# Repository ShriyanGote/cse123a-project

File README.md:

# 123a-project: Smart Pitcher Base

This repo contains all the code, hardware notes, and documentation for our Smart Pitcher Base project. The system is made up of three pieces:

1. **ESP32C3 firmware** — reads the load cell (HX711) on the pitcher base and POSTs readings to the web server.
2. **Web server / dashboard** — a Vite + React app (deployed on Vercel) that ingests readings into Supabase. Account sign-in and a setup guide live at https://cse123a-project-6a3s.vercel.app/.
3. **Mobile app** — an Expo / React Native app that talks to the web server, displays the water level, and receives low-water push notifications.

Everything lives under [`Code/`](Code). Each sub-project has its own README with run instructions.

```
Code/
├── ESP32/         # firmware (ESP-IDF)
├── web-server/    # Vite + React dashboard + Vercel API routes
├── mobile-app/    # Expo / React Native app
└── 3D Designs/    # printable parts for the base
```

---

# Other things in this repo

- [Documentation/](Documentation) — write-ups and design docs
- [Hardware Notes/](Hardware%20Notes) — schematics, PCB revisions, wiring notes
- [HardwarePicture/](HardwarePicture) — photos of the assembled hardware
- [Meeting Notes/](Meeting%20Notes) — weekly meeting notes
- [Status Updates/](Status%20Updates) — milestone / status reports
- [Code/Links to Test Cases.md](Code/Links%20to%20Test%20Cases.md) — index of test cases
- `git-contribution-report.sh` + `aliases.json` + `folders.json` — helpers for generating per-author contribution metrics

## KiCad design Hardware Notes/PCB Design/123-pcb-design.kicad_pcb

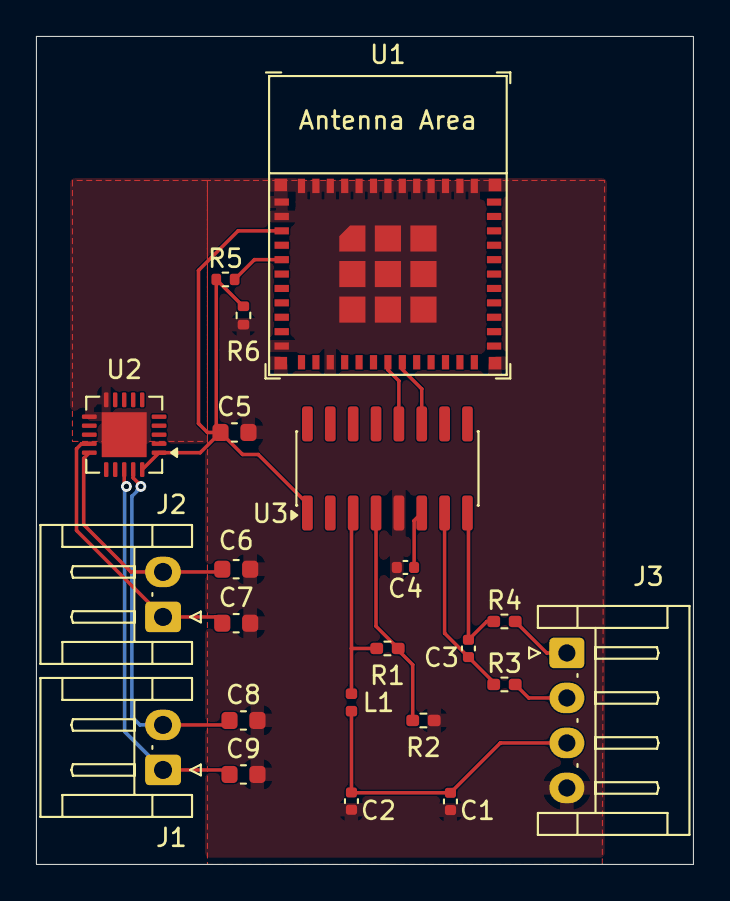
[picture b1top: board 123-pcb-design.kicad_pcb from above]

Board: 2 copper layers, 36.5 x 46.0 mm, 22 parts (0 on the bottom side), 17 nets.

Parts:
C1, C3, C4: 0.1μF; C_0402_1005Metric
C2: 10μF; C_0402_1005Metric
C5, C6, C7: 4.7μF; C_0603_1608Metric
C8, C9: 10μF; C_0603_1608Metric
J1, J2: JST 1x02; JST_EH_S2B-EH_1x02_P2.50mm_Horizontal
J3: JST 1x04; JST_EH_S4B-EH_1x04_P2.50mm_Horizontal
L1: 3.3μH; L_0402_1005Metric
R1, R2: 20k; R_0402_1005Metric_Pad0.72x0.64mm_HandSolder
R3, R4: 100; R_0402_1005Metric_Pad0.72x0.64mm_HandSolder
R5: 100k; R_0402_1005Metric
R6: 100K; R_0402_1005Metric
U1: ESP32-C3-MINI-1
U2: MCP73871; QFN-20-1EP_4x4mm_P0.5mm_EP2.5x2.5mm
U3: HX711; SOIC-16_3.9x9.9mm_P1.27mm

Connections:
GND: C1.2, C2.2, C4.2, C5.2, C6.2, C7.2, C8.2, C9.2, J3.4, R2.2, R6.2, U1.1 (GND), U1.2 (GND), U1.11 (GND), U1.14 (GND), U1.36 (GND), U1.37 (GND), U1.38 (GND), U1.39 (GND), U1.40 (GND), U1.41 (GND), U1.42 (GND), U1.43 (GND), U1.44 (GND), U1.45 (GND), U1.46 (GND), U1.47 (GND), U1.48 (GND), U1.49 (GND), U1.50 (GND), U1.51 (GND), U1.52 (GND), U1.53 (GND), U2.10 (V_{SS}), U2.11 (V_{SS}), U2.21 (V_{SS}), U3.5 (AGND)
GPIO_4/ADC_1: U1.18 (GPIO4/ADC1_CH4), U3.12 (DOUT)
GPIO_5/ADC_2: U1.19 (GPIO5/ADC2_CH0), U3.11 (PD_SCK)
J3_Pin_1: J3.1, R4.2
J3_Pin_2: J3.2, R3.2
J3_Pin_3: C1.1, C2.1, J3.3, L1.2
unnamed: R5.2, U1.5 (GPIO2/ADC1_CH2)
unnamed: C7.1, J2.1, U2.14 (V_{BAT})
unnamed: L1.1, R1.1, U3.3 (AVDD)
unnamed: C3.2, R4.1, U3.8 (INA+)
unnamed: C3.1, R3.1, U3.7 (INA-)
unnamed: C4.1, U3.6 (VBG)
unnamed: R1.2, R2.1, U3.4 (VFB)
U2-J1_NEG: C8.1, J1.2
U2-J1_POS: C9.1, J1.1, U2.18 (IN)
U2-V_{BAT}-Pad15: C6.1, J2.2, U2.15 (V_{BAT})
VSUP: C5.1, U1.3 (3V3), U2.1 (OUT), U2.20 (OUT), U3.1 (VSUP)

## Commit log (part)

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2026-02-22 Test
2026-02-22 Create status report 5
2026-02-22 Implement firebase sdk for cloud messaging push notifications
2026-02-22 Push notification test
2026-02-24 Naming convention changes
2026-02-24 initial planning for server side calculations
2026-02-24 mac bs
2026-02-24 Adding demo script
2026-02-24 Updating Demo script
2026-02-24 updated architecture diagram
2026-02-24 Adding Engineering drawings for base plate
2026-02-24 Restructured documentation sections and updated design files
2026-02-24 fixing formating
2026-02-24 started documentation of hx711
2026-02-25 added HX711tex to design
2026-02-25 rm section made subsection
2026-02-25 Fixed names, + calibrating
2026-02-25 rm build + calibrated
2026-02-26 Shows raw data, offset, weightChange, grams not calibrated not actual grams
2026-02-26 Update Brita calibration UI
2026-02-27 Added reset calibration button
2026-02-27 Created test directory and unit tests for app
2026-02-27 Updated README with test instructions
2026-02-27 Fixing document not compiling
2026-02-27 adding my contributions to status updates
2026-02-28 Updated individual contribution for status 5
2026-02-28 adding Whats next to status report
2026-02-28 fixing spacing
2026-02-28 combo layout w/ Initial Prototype layout
2026-02-28 fixing layers and web vs phone
2026-02-28 status doc updated
2026-02-28 working on
2026-02-28 Updated what we did for status 5
2026-02-28 Updated status 5 with repo link
2026-02-28 header file prep for test code
2026-03-02 simulator file
2026-03-02 Removed fcm logic and reimplement with Push API from web-push
2026-03-02 Updating thickness to drawings
2026-03-02 Created an exploded view of the sensor with plates
2026-03-02 adding sustainablity statement
2026-03-03 Edit Architecture_Diagram.svg to remove the word ESP
2026-03-03 fixed formatting/section stuff
2026-03-03 fixed table of contents
2026-03-03 Made the plate thicker and added flat bottom
2026-03-03 tester code working
2026-03-03 Moved app test to src directory
2026-03-03 Updated Web App Section in Design Doc
2026-03-03 Added more to webapp section in design doc
2026-03-03 lineweight and separation
2026-03-03 Block Diagram included in main pdf file
2026-03-03 Updated architecture of webapp on design doc
2026-03-03 Small comments on what to add to testing section in design doc
2026-03-04 added structure, added my focus
2026-03-04 adding Aesthetic prototype section
2026-03-04 Adding pdf
2026-03-04 Updating todos
2026-03-04 Reorganized wifi provisioning code (not functional yet)
2026-03-04 fixedtypos
2026-03-05 Restructure main, ready for wifi http implement
2026-03-05 working wifi + http ?
2026-03-05 Creating Status 6
2026-03-05 HTTP POST WORKS harded code network for now
2026-03-05 modified design doc
2026-03-05 used Implementation I wrote
2026-03-05 basic collab idea
2026-03-05 Added debug statements to setupPushNotifications
2026-03-05 Add vite public key
2026-03-05 Added debug to ingest push notifications
2026-03-05 Push Debug
2026-03-05 microcontroller testing info updated
2026-03-05 updated appendix section
2026-03-05 status report updates
2026-03-05 Edit Status-6.tex
2026-03-05 Adding my contirubtions for status report
2026-03-06 Updated individual section in status 6
2026-03-07 updated status doc for submission
2026-03-07 status update
2026-03-07 finished status
2026-03-07 Doing Design for Manufacture
2026-03-09 http section
2026-03-09 section 4 of demo
2026-03-09 added to div of labor section
2026-03-09 Updated design doc
2026-03-10 Sync repo with current web app implementation
2026-03-10 Center enable notification button
2026-03-10 Added web app test section
2026-03-10 added test server for esp
2026-03-10 Added notification section to demo script
2026-03-10 Replaced all instances of esp32 and brita with appropriate terms
2026-03-10 added design obj
2026-03-10 added to design pdf
2026-03-10 added brita accident
2026-03-11 Add new file
2026-03-11 made a design for the washer
2026-03-12 documents split in two
2026-03-12 added title page
2026-03-12 Adding my individual contribituions
2026-03-12 added grams to test server display
2026-03-12 Edit Links to Test Cases
2026-03-12 Used my hotspot
2026-03-13 revision changes to prototype doc
2026-03-13 Added my individual contributions to design doc
2026-03-13 Added edge cases to test file
2026-03-13 Added unit tests for notification logic
2026-03-13 Added more edge cases
2026-03-13 Updated evaluation web app testing section
2026-03-13 Updated web app testing section
2026-03-13 Updated test cases
2026-03-13 Added executive summary
2026-03-13 team reflections
2026-03-13 Added team reflection part
2026-03-13 Remove brita from title
2026-03-13 Completed webapp functional prototype section
2026-03-13 First edit
2026-03-13 team reflections and removed mentions of esp32
2026-03-13 added detailed test cases for test plan
2026-03-13 Adding my contributions to design doc
2026-03-14 Updating renderings
2026-03-14 adding the renderings to the design doc
2026-03-14 finished wire diagram
2026-03-14 reflectipons + division of labor
2026-03-14 wiring diagram update
2026-03-14 div labor shriyan
2026-03-14 design review
2026-03-14 div of labor
2026-03-14 added link to test cases to design doc
2026-03-14 compiled design doc
2026-03-16 added overview section to demo script
2026-03-17 demo script
2026-03-18 updating demo
2026-03-18 Changed notifications to send everytime weighed value is below 20%
2026-03-18 Updated notification section in demo script
2026-03-18 adding Live demo + hardware
2026-03-18 Quick calibration refresh fix
2026-03-19 demo script w/ need and goal
2026-03-19 Add website and code repo url to Code README
2026-03-19 part 4 software changes
2026-03-19 updated pdf
2026-03-19 adding time
2026-03-19 adding time for live demo
2026-03-19 last minute update
2026-03-19 need/goal
2026-04-08 setting up document to be about production design and not prototype
2026-04-08 meeting notes
2026-04-09 attempting to add https functionality
2026-04-09 added contribution metrics script
2026-04-09 Add contribution report script
2026-04-09 Edit git-contribution-report.sh
2026-04-09 modified contribution metrics script
2026-04-11 battery charging information, mfr design updates
2026-04-11 pcb prototype setup
2026-04-11 USBC connector and HX711 wiring
2026-04-13 amplifier circuit added
2026-04-13 adding compartment for base
2026-04-13 Adding lid for compartment
2026-04-14 mobile app
2026-04-14 added 4/6 meeting notes
2026-04-14 adding exploded view with housing
2026-04-14 adding assembled_v1 design
2026-04-15 mobile app api
2026-04-16 updated to v1 circuit
2026-04-16 custom board documentation in progress
2026-04-17 updates to pcb design section
2026-04-17 added HTTPS capabilities, automatic wifi reconnection
2026-04-18 prep for tests
2026-04-18 Started tests for functions
2026-04-18 updated design for housing
2026-04-18 moved opening down
2026-04-19 design section updates and reorganizing testing/design information
2026-04-21 Implemented basic login auth, dashboard and groups
2026-04-22 removed self-hosted section, changed HTTP to HTTPS capabilities in design doc
2026-04-22 Improved dashboard and groups interface
2026-04-23 more on custom PCB added, rev2 coming by end of week
2026-04-23 Added notches to make sure the plate doesnt fall out
2026-04-23 added new base plate design
2026-04-23 Lowered the shelf
2026-04-23 simple BLE provisioning
2026-04-25 amplifier system design
2026-04-25 simplified provisioning code
2026-04-26 provisioning through https jwt jwe
2026-04-27 functionalized wifi provisioning, basic reconnect ability
2026-04-28 Updating for compartment section
2026-04-28 more ds
2026-04-28 Created screen to introduce users to the app and animated ui
2026-04-28 Changed group member cards to show user display names instead of user id
2026-04-28 Rename api route files
2026-04-28 Remove direct query from client side
2026-04-28 Remove admin role, allow ownership transfer and remove group members as owner
2026-04-29 provisioning short term reconnection, need to add long term
2026-04-29 section for housing
2026-04-29 Edit README.md
2026-04-30 base plate desing
2026-04-30 Add custom BLE provisioning flow across app, backend, and ESP firmware.
    This aligns QR/BLE onboarding with hardcoded UUIDs, token-based device registration, and ESP32 custom GATT provisioning so iOS dev builds can provision and ingest reliably.
    Made-with: Cursor
2026-04-30 Reduce web-server function count for Vercel Hobby.
    This removes legacy provisioning session endpoints and the unused mobile client helpers so the deployment can stay within the 12 serverless function limit.
    Made-with: Cursor
2026-05-01 removing files
2026-05-02 Memory saved on power loss
2026-05-02 adding test code for api for web-server
2026-05-02 made top plate wider
2026-05-03 board rev3
2026-05-05 poster file added
2026-05-05 Updated design/renamed designs
2026-05-05 added hole for wire passthrough
2026-05-05 making walls higher'
2026-05-06 removing 2
2026-05-06 Adding feature where users can deactive/activite their accounts via web-app
2026-05-06 Adding guide
2026-05-06 Adding guide/insturctions for webapp
2026-05-06 Update 2 files
    - /5_6_communication_diagram.png
    - /Meeting Notes/5_6_communication_diagram.png
2026-05-06 Upload prov diagram meeting notes
2026-05-06 moved prov diagram
2026-05-07 Implement expo notifications to mobile app
2026-05-08 Upload provisioning diagram
2026-05-08 Upload architecture diagram
2026-05-08 BLE + Main
2026-05-08 renamed diagrams
2026-05-08 main+ble
2026-05-08 adding more
2026-05-09 updates for design section
2026-05-11 Configured mobile app notifications
2026-05-11 Reconfigured notfications
2026-05-12 Added test coverage and lint check to webserver and mobile app
2026-05-12 poster added, pcb rev3 updated
2026-05-12 feat: Add aliases and folders for contribution metrics
2026-05-12 Updating Readme
2026-05-12 Refactor BLE for Wifi
2026-05-12 Edited poster
2026-05-12 Edited poster again
2026-05-13 updated poster
2026-05-13 Added README for local mobile app setup and delayed notiifications when user is refilling water (30 second buffer when at 0%)
2026-05-13 Modified mobile app README
2026-05-14 updated system architecture diagram
2026-05-14 Updated poster pdf
2026-05-14 Fix ingest to multiple groups with the same device id
2026-05-14 started demo script
2026-05-14 Provision wifi timeout
2026-05-14 updated demo script
2026-05-14 Added tests for webserver
2026-05-15 pcb rev 4 w/ battery monitor circuit
2026-05-15 removed resistor from voltage supply path
2026-05-15 Added mobile app tests
2026-05-15 Made walls 4mm higher
2026-05-15 Webpage section
2026-05-15 Adding siginning out everywhere
2026-05-15 changed user to token
2026-05-15 adding a sign out everywhere feature
2026-05-15 Add delete account functionality
2026-05-15 edited script
2026-05-15 Kick mobile app users back to login screen after sign out everywhere
2026-05-15 Add reactivate account functionality
2026-05-15 Help
2026-05-16 Update mobile app setup README
2026-05-17 Made USB hole wider
2026-05-17 intro and calibration edited
2026-05-17 schematic added to PCB design
2026-05-17 amplifier test section adjusted to be more general
2026-05-18 fixing pocket sizes
2026-05-18 Fridays work
2026-05-18 Updating webpage part
2026-05-18 Account deletion
2026-05-18 Added account creation message
2026-05-21 Fix lint errors in webserver
2026-05-24 adding schematic slide
2026-05-29 Updated web app section
2026-05-30 Add new directory
2026-05-30 power design
2026-06-02 DRC passes for schematic
2026-06-02 new pcb documents, references added to schematic
2026-06-07 updated doc test cases, reflections, division of labor sections
2026-06-08 Updated Mobile App Setup Readme
2026-06-08 added prototype images to design doc
2026-06-08 changes to design doc
2026-06-09 Updated mobile app section in design doc
2026-06-09 Updated web app section on design doc
2026-06-09 Updating diagrams
2026-06-09 Adding my reflection
2026-06-09 PCB picture for document
2026-06-09 adding divison of labor
2026-06-09 updating
2026-06-09 Update web app in design doc
